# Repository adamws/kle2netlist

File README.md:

# kle2netlist

|         |                                                                                                                                                                                                                                                                                                                                                                                                                                                                                                                                                                                                                    |
| ---     | ---                                                                                                                                                                                                                                                                                                                                                                                                                                                                                                                                                                                                                |
| CI/CD   |                                                                                                                                                                                                                                                                                      |
| Package |                                                                                                                                                                                                                                                                                                                                                                                                                                                                                                            |
| Meta    |      |

-----

**KiCad netlist generator for mechanical keyboards**

## Installation

```
pip install kle2netlist
```

## Usage

```
$ kle2netlist --help

Usage: kle2netlist [OPTIONS]

Generates KiCad netlist for a given keyboard layout json file.

Options
--layout                Path to kle layout file [default: None] [required]
--output                Output netlist file [default: keyboard.net]
--switch-footprint      Switch footprint f-string [default: PCM_Switch_Keyboard_Cherry_MX:SW_Cherry_MX_PCB_{:.2f}u]
--stabilizer-footprint  Stabilizer footprint f-string, optional [default: PCM_Mounting_Keyboard_Stabilizer:Stabilizer_Cherry_MX_{:.2f}u]
--diode-footprint       Diode footprint [default: Diode_SMD:D_SOD-123F]
--lib-path              Path to symbol library [default: None]
--controller-circuit    Name of controller circuit [default: None]
--extra-circuits        Extra circuits [default: None]
--row-column-pin-order  Comma separated list of microcontroller pins defining order of row/column assignments [default: None]
--version               Prints the version of the kle2netlist package.
--help                  Show this message and exit.
```

### Controller circuit templates

<table>
    <tr>
        <td style="width:40%" align="center"><b>Name and description</b></td>
        <td align="center"><b>Layout</b></td>
    </tr>
    <tr>
        <td>atmega32u4_v1:<br>[todo]</td>
        <td align="center"></td>
    </tr>
    <tr>
        <td>atmega32u4_v2:<br>[todo]</td>
        <td align="center"></td>
    </tr>
</table>

### Extra circuit templates

<table>
    <tr>
        <td style="width:40%" align="center"><b>Name and description</b></td>
        <td align="center"><b>Layout</b></td>
    </tr>
    <tr>
        <td>usb_minimal:<br>[todo]</td>
        <td align="center"></td>
    </tr>
    <tr>
        <td>usb_udb_clone:<br>[todo]</td>
        <td align="center"></td>
    </tr>
</table>

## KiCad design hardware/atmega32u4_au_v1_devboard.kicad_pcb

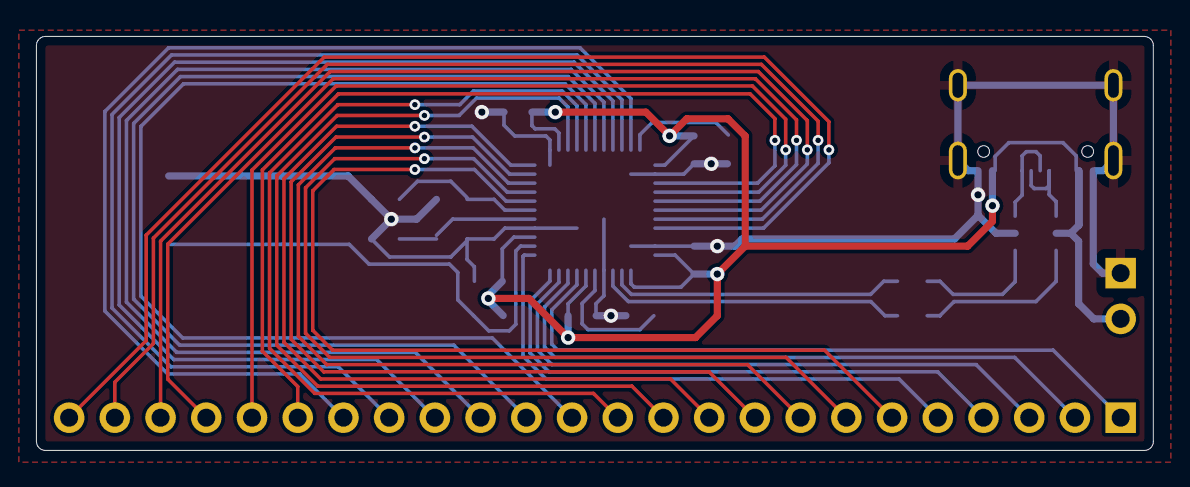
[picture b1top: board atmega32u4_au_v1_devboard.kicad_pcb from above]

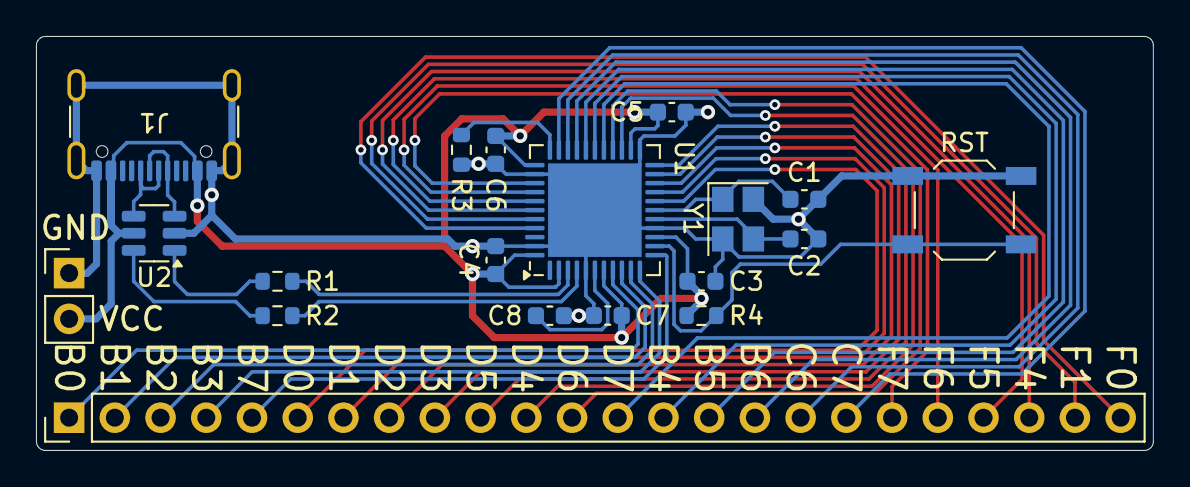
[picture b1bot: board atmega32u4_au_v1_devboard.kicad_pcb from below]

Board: 2 copper layers, 62.0 x 23.0 mm, 19 parts (19 on the bottom side), 37 nets.

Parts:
C1, C2: 22p; C_0603_1608Metric
C3, C4, C5, C6: 0.1u; C_0603_1608Metric
C7: 4.7u; C_0603_1608Metric
C8: 1u; C_0603_1608Metric
J1: USB_C_Receptacle_USB2.0_14P; USB_C_Receptacle_GCT_USB4105-xx-A_16P_TopMnt_Horizontal
J2: Conn_01x24_Pin; PinHeader_1x24_P2.54mm_Vertical
J3: Conn_01x02_Pin; PinHeader_1x02_P2.54mm_Vertical
R1, R2: 22; R_0603_1608Metric
R3, R4: 10k; R_0603_1608Metric
RST: SW_SPST; SW_SPST_TL3342
U1: ATmega32U4-M; QFN-44-1EP_7x7mm_P0.5mm_EP5.2x5.2mm
U2: TPD2S017; SOT-23-6
Y1: Crystal_GND24; Crystal_SMD_3225-4Pin_3.2x2.5mm

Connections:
GND: C1.2, C2.2, C3.2, C4.2, C5.2, C6.2, C7.2, C8.2, J1.A1, J1.A12, J1.B1, J1.B12, J1.S1, J3.1, R3.2, RST.1, U1.5, U1.15, U1.23, U1.35, U1.43, U1.45, U2.2, Y1.2, Y1.4
VCC: C3.1, C4.1, C5.1, C6.1, C7.1, J1.A4, J1.A9, J1.B4, J1.B9, J3.2, R4.2, U1.2, U1.7, U1.14, U1.24, U1.34, U1.44, U2.5
io0: J2.1, U1.8
io1: J2.2, U1.9
io2: J2.3, U1.10
io3: J2.4, U1.11
io4: J2.14, U1.28
io5: J2.15, U1.29
io6: J2.16, U1.30
io7: J2.5, U1.12
io8: J2.17, U1.31
io9: J2.18, U1.32
io10: J2.6, U1.18
io11: J2.7, U1.19
io12: J2.8, U1.20
io13: J2.9, U1.21
io14: J2.11, U1.25
io15: J2.10, U1.22
io16: J2.12, U1.26
io17: J2.13, U1.27
io18: J2.24, U1.41
io19: J2.23, U1.40
io20: J2.22, U1.39
io21: J2.21, U1.38
io22: J2.20, U1.37
io23: J2.19, U1.36
mcu/D+: R2.1, U1.4
mcu/D-: R1.1, U1.3
mcu/UCAP: C8.1, U1.6
mcu/XTAL1: C1.1, U1.17, Y1.1
mcu/XTAL2: C2.1, U1.16, Y1.3
mcu/~HWB/PE2: R3.1, U1.33
mcu/~RESET: R4.1, RST.2, U1.13
u2/D+: R2.2, U2.6
u2/D-: R1.2, U2.1
usb/D+: J1.A6, J1.B6, U2.4
usb/D-: J1.A7, J1.B7, U2.3

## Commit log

2021-01-24 add cli options
    - added -l which can specify additional search paths
2021-01-26 handle different key widths
    - currenlty only MX_Alps_Hybrid library is supported, hence
    in __main__ it is hardcoded
2021-02-07 add support for new switch library
    - for Switch_Keyboard library stabilizer mounting holes are not part of
    switch footprint and need to be added separately
2021-02-09 add support for MX/Alps hybrid footprints
2021-02-09 add support for Alps footprints
2021-02-11 add stabilizers for hybrid switches
2021-02-11 better tests
    - reset internal skidl circuit for each kle2netlist call
    - compare generated netlist with reference
2021-02-14 add support for iso enter
2021-02-14 add ninja2 to dev-dependencies
    - bump versions
2021-02-14 template based testing
    - replaced netlist for each parameter combination with templates
2021-02-17 update iso enter footprints details
    also update perigoso library name which has changed
2021-03-05 generation of atmega circuit
    add simple ATmega32U4-AU circuit to the netlist. It consist uc,
    decoupling capacitors, usb type C with esd protection, crystal
    oscillator and reset button. Row and columns are assigned to the pins in
    following order: PB0-7, PC6, PC7, PD0-7, PF0-7
2021-03-05 bump versions
2021-03-05 Added kicad pcb template for atmega32u4 circuit
2021-03-09 change USB-C plug to receptacle, update template
2021-03-11 name nets in controller circuit, update template
2021-03-25 add xml netlist generation
2022-08-14 Update dependencies
    Updated `typer`, `rich` and `Jinja2`, regenerated `poetry.lock`, this
    solves `poetry run safety check` issues.
2022-08-14 Add python 3.9 and 3.10
2022-08-14 Add KiCad symbols as submodule
    Bundle KiCad v5 symbols with package and use them as defaults (last in
    `skidl.lib_search_paths` list). This way this package should run without
    KiCad installed.
2022-08-14 Add check for key label value
2022-12-31 Update poetry installation method
2022-12-31 Ignore safety and style
2023-03-08 Update to SKiDL 1.0.0 and use kicad v6 library
2023-03-08 Add microcontroller VBUS pin (7) to VCC net
2023-03-18 Update version number
2023-08-17 Update dependencies
2023-08-19 Fix stabilizer footprint names
2024-01-03 Migrate to hatch build system
2024-01-03 Enable coverage report upload
2024-01-03 Minor linting fixes
2024-01-03 Code formatting
2024-01-03 Fix minor ruff errors
2024-01-03 Raise meaningful error when requested too big key matrix
2024-01-03 Automatic fix of labels with whitespaces
2024-01-04 Add alias for kiswitch library
2024-01-05 Change default footprint library and limit footprint choices
2024-01-05 Add option to select diode footprint
2024-01-05 Remove python versions badge
2024-01-10 Add hotswap kailh mx footprint support
2024-01-10 Remove handling specific libraries
    From now on, pass everything what is needed via arguments (or CLI
    interface). This allows to use footprints which were not explicitly
    added so the version of kle2netlist does not have to be updated
    constantly). There are drawbacks though:
    - no ISO specific switch added anymore (don't want to add yet another
    argument for `--iso-switch-footprint`)
2024-06-05 Update build workflow
2024-06-12 Update to development version of skidl and use KiCad 8 libs
2024-06-12 Use utf-8 encoding when opening layout files
    Fixes #3
2024-06-12 Add some type annotations
2024-06-12 Use kbplacer keyboard class to support alternative layouts
    Use `MatrixAnnotatedKeyboard` from `kbplacer` in order to support
    layouts with alternative keys. Use layout collapsing in case multiple
    keys share single matrix (logical) position.
2024-06-12 Move microcontroller subcircuit to separate file
2024-06-12 Move footprints to dictionary
2024-06-12 Add support for controller circuit variants
2024-06-12 Add netlist generation with CLI test
2024-06-12 Update help
2024-06-12 Do not use default skidl circuit object
2024-06-14 Organize functions into multiple files
2024-06-14 Add hatch script to generate circuit kicad_pcb template
2024-06-14 Transfer `kicad-templates/atmega32u4-au-v1` to positions in code
    This commit retrieves elements positions from an old template
    and uses them in `circuits/atmega32u4.py` when generating new template.
    This is step towards generating templates at runtime (which can be
    parametrized) instead of using hand-crafted kicad files.
2024-06-15 Simplify layout templates footprint position handling
2024-06-15 Add `.justfile`
2024-06-15 Add svg image of `atmega32u4_au_v1` template
2024-06-19 Handle silkscreen reference relative positions
2024-07-23 Add comment about decoupling capacitors
2024-07-23 Update silkscreen annotations positions
2024-07-23 Add v2 circuit variant based on JP60 keyboard
2024-07-23 Do not version generated `kicad_pcb` files and generate v2 svg
2024-07-23 Update `kbplacer` version
2024-07-24 Update template elements positions
2024-07-25 Update positions
2024-07-25 Add tracks template
2024-07-25 Remove v1 template and rename v2 to v1
2024-07-25 Rotate `R4` and minor tracks update
2024-07-25 Connect `U1` thermal pad to GND
2024-07-31 Sort tracks
2024-08-02 Move C7 and C8, add tracks and add initial via support
2024-08-02 Cleanup tracks
2024-08-04 Add optional `offset` support
2024-08-04 Use `ControllerCircuit` for generating template
2024-08-30 Add option to define order of pin matrix assignments
2024-08-30 Add fake rows to consume all io pins
    This will allow for preparation of fanout template traces
2024-08-30 Minor changes for tracks in bottom portion of circuit
2024-08-30 Add git diff action
2024-08-30 Ignore tracks of `io` nets.
    Existence of these tracks depends on keyboard matrix size and pin
    assignments. Tracks for matrix pins will be added to template but will
    be conditional and will be stored in separate collection.
2024-08-30 Change default via size
2024-08-31 Start implementation on IO fanout tracks
2024-08-31 Move `C5` capacitor
2024-08-31 Add fanout tracks for IO pads
2024-08-31 Fix via clearance issue near USB connector
2024-08-31 Minor changes in USB tracks
2024-08-31 Move USB label
2025-03-15 Change default USB footprint
2025-03-15 Update SKiDL
2025-03-16 Add support for KiCad 9
2025-03-25 Use nanometers internally and round template position values
2025-04-03 Introduce using multiple sub-circuits
2025-04-03 Fix `kle2netlist.pcb` module and move circuit template generation
2025-04-03 Normalize positions in `usb` template
2025-04-08 Add support for setting via dimensions
2025-04-08 Add second USB circuit variant based on UDB
2025-04-08 Flip UDB based USB circuit to bottom side
2025-04-10 Add second variant of atmega32u4 circuit
2025-06-09 Remove unused imports
2025-06-09 Move KiCad specific code to separate file
2025-06-10 Move templates generation to package's main
    Remove special tools/templates.py and replace it by calling package's
    main. Generating netlist which combines key matrix, controller circuit
    and extra circuits should work now. Applying templates does not work
    (i.e. moving positions and adding tracks) if there is more than one
    merged interface because annotations would not match template and final
    board.
2025-06-12 Implement combining multiple circuits
2025-06-12 Add example completed PCB which uses circuit templates
2025-06-13 Rename reference mapping variable
2025-06-13 Support applying template with rotation
2025-06-13 Place fanout tracks only for pads with nets assigned
2025-06-13 Add `extra_libraries` argument to `generate_pcb`
2025-06-26 Reorder fanout tracks for v1 layout
2025-06-26 Fix fanout track to pin assignments for v2
2025-06-26 Update ruff usage
2025-06-26 Introduce `MatrixType` option
2025-06-26 Better prints for fanout tracks obtained from template board
2025-06-26 Update v2 layout to make more space on the corners
2025-07-11 Minor tracks cleanup
2025-07-15 Minor changes to udb clone template
    Increased size of vias, minor tracks adjustments and fix unassigned
    net for ESD IC pads.
2025-07-15 Add example which uses usb template to generate usb-jst PCB
2025-07-16 Move `F1` and `D1` for `udb_clone` template
2025-07-16 Make adding fanout tracks optional
2025-07-16 Handle template rotations
2025-07-16 Fix JST connector footprint
    Correct footprint would not fit with old template position.
    I would need to adjust template to move components
    closer to each other or move whole template up.
    I decided to do the latter.
    PCB dimensions and mounting hole positions are still UDB board
    compatible but the usb connector now sticks out about 1.3mm
2025-07-16 Add 3d models
2025-07-16 Add missing `requirements.txt`
2025-07-16 Add script which generate simple result presentation page
2025-07-17 Add deployment of results to vercel
